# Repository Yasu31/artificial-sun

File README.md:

# Artificial Sun
[English README](/README-en.md)

自然な明かりで朝起きれる小型デバイス

ここではファームウェアのArduinoスケッチと基板デザイン(KiCad)を公開しています
- プロジェクト: https://yasunori.jp/pocket-sunrise
- 外装部品: https://grabcad.com/library/pocket-sunrise-1
- 動画: https://youtu.be/eCHGJ3ehzJc

## 電子部品
必要な電子パーツはこちらのスプレッドシートにまとめてあります。すべて秋月電子で買えます。
 →[Artificial Sun 電子部品](https://docs.google.com/spreadsheets/d/1AGpVGOaxi01ax8kF4fcREE8NY4uzkjkZFQBg4IJ91os/edit?usp=sharing)

## 基板
私はPCBGOGOに発注しましたがどこでも大丈夫だと思います。5枚発注して（初回割ということもありましたが）送料込みでたった1200円でした。

## 基板実装
以下の写真を参考に実装してください。注意点としては
- LEDの定格内で扱っていて、抵抗での発熱も許容範囲のはずですが、それでも想定外のケースなどで異常発熱する場合もあり得るので、使用時は常にそばにいる状態にしてください。自己責任で使ってください。
- 7セグ用の300Ω抵抗は一部のみ使い、それ以外は短絡してください（7セグの向きを後から変えられるようにこの実装になっています）。
- LEDの定格電流的には25Ωの電流制限抵抗は全然許容範囲内なのですが、セメント抵抗の方の発熱が大きかったので、50Ω抵抗を並列で接続して放熱板も取り付けることで発熱を抑えています。画像のように組付ければ、外装パーツ内に収まるはずです（もちろんちゃんとしたLEDドライバを使えば発熱を抑えられるのですが、初めての基板設計ということもあり簡単な回路を優先しました）
- Arduino nanoが基板に挿さったままだとスケッチが書き込めない場合があります。うまく書き込めない場合は、一旦抜いてから書き込んでください。
- LEDは10センチほどのワイヤで基板に接続してください。曲げやすいワイヤの方が外装パーツに挿入しやすいです。
- M3、長さ12mmのナットとボルト4本で組み立てられます。ゴム足パーツを底に貼ると滑り止めになります。

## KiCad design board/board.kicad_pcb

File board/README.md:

high-power LED circuit from https://nobulabo.com/power-led-blink/

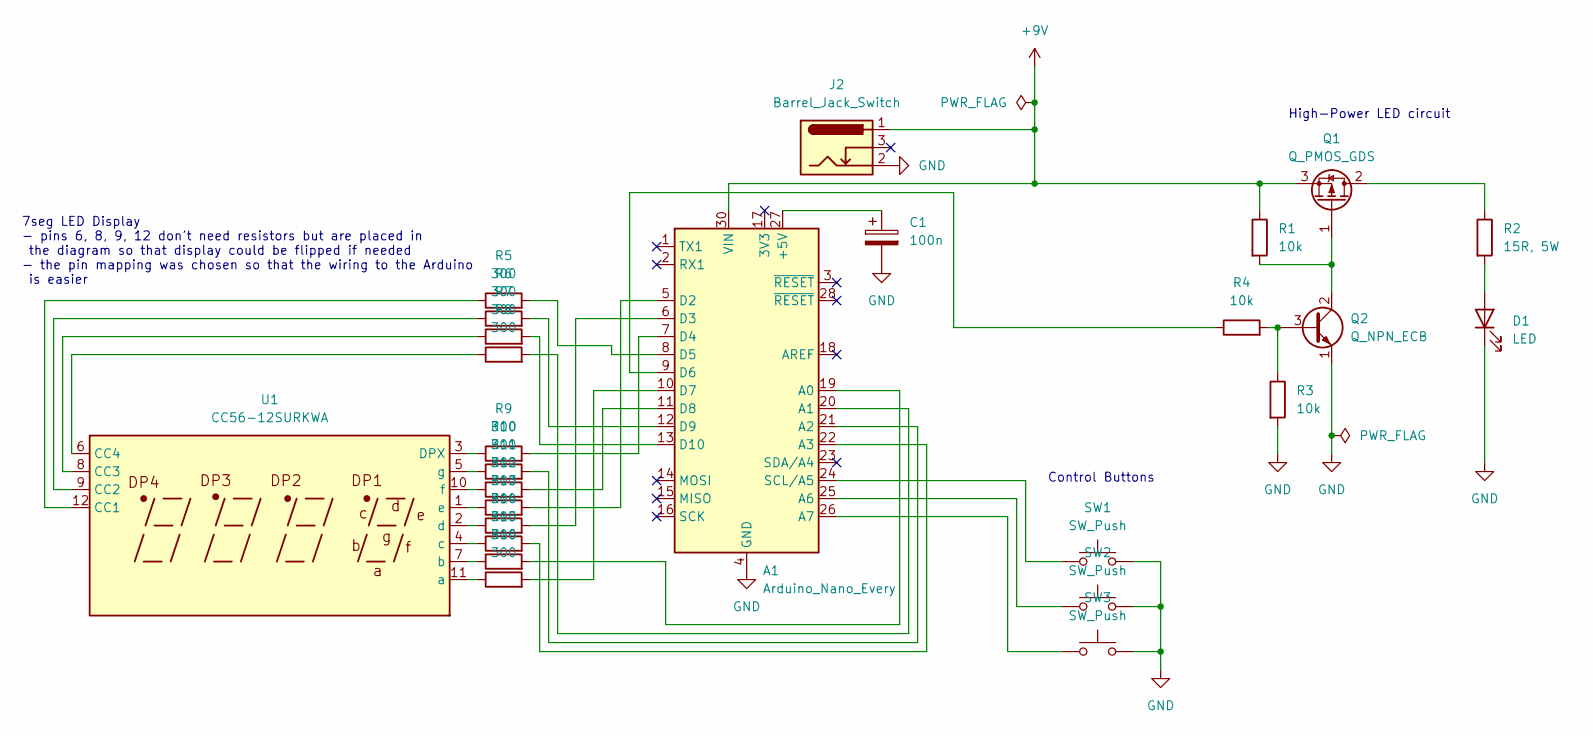
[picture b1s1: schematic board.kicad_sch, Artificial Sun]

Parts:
A1: Arduino_Nano_Every; Arduino_Nano
C1: 100n; C_Disc_D7.0mm_W2.5mm_P5.00mm
D1: LED; PinHeader_1x02_P2.54mm_Vertical
J2: Barrel_Jack_Switch; BarrelJack_Horizontal
Q1: Q_PMOS_GDS; TO-220-3_Horizontal_TabDown
Q2: Q_NPN_ECB; TO-92
R1, R3, R4: 10k; R_Axial_DIN0207_L6.3mm_D2.5mm_P10.16mm_Horizontal
R2: 15R, 5W; R_Axial_Power_L20.0mm_W6.4mm_P30.48mm
R5, R6, R7, R8, R9, R10, R11, R12, R13, R14, R15, R16: 300; R_Axial_DIN0207_L6.3mm_D2.5mm_P10.16mm_Horizontal
SW1, SW2, SW3: SW_Push; SW_PUSH_6mm_H7.3mm
U1: CC56-12SURKWA; CA56-12SURKWA

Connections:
+9V: A1.30 (VIN), J2.1, Q1.3 (S), R1.1
GND: A1.4 (GND), A1.29 (GND), C1.2, D1.1 (K), J2.2, Q2.1 (E), R3.2, SW1.2, SW2.2, SW3.2
unnamed: A1.27 (+5V), C1.1
unnamed: A1.19 (A0), R15.2
unnamed: A1.20 (A1), R8.2
unnamed: A1.21 (A2), R10.2
unnamed: A1.22 (A3), R14.2
unnamed: A1.25 (A6), SW2.1
unnamed: A1.26 (A7), SW3.1
unnamed: A1.5 (D2), R12.2
unnamed: A1.6 (D3), R13.2
unnamed: A1.7 (D4), R9.2
unnamed: A1.8 (D5), R5.2
unnamed: A1.9 (D6), R4.1
unnamed: A1.10 (D7), R16.2
unnamed: A1.11 (D8), R11.2
unnamed: A1.12 (D9), R6.2
unnamed: A1.13 (D10), R7.2
unnamed: A1.24 (SCL/A5), SW1.1
unnamed: D1.2 (A), R2.2
unnamed: Q1.2 (D), R2.1
unnamed: Q1.1 (G), Q2.2 (C), R1.2
unnamed: Q2.3 (B), R3.1, R4.2
unnamed: R5.1, U1.12 (CC1)
unnamed: R6.1, U1.9 (CC2)
unnamed: R7.1, U1.8 (CC3)
unnamed: R8.1, U1.6 (CC4)
unnamed: R9.1, U1.3 (DPX)
unnamed: R16.1, U1.11 (a)
unnamed: R15.1, U1.7 (b)
unnamed: R14.1, U1.4 (c)
unnamed: R13.1, U1.2 (d)
unnamed: R12.1, U1.1 (e)
unnamed: R11.1, U1.10 (f)
unnamed: R10.1, U1.5 (g)

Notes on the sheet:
7seg LED Display - pins 6, 8, 9, 12 don't need resistors but are placed in the diagram so that display could be flipped if needed - the pin mapping was chosen so that the wiring to the Arduino is easier
High-Power LED circuit
Control Buttons

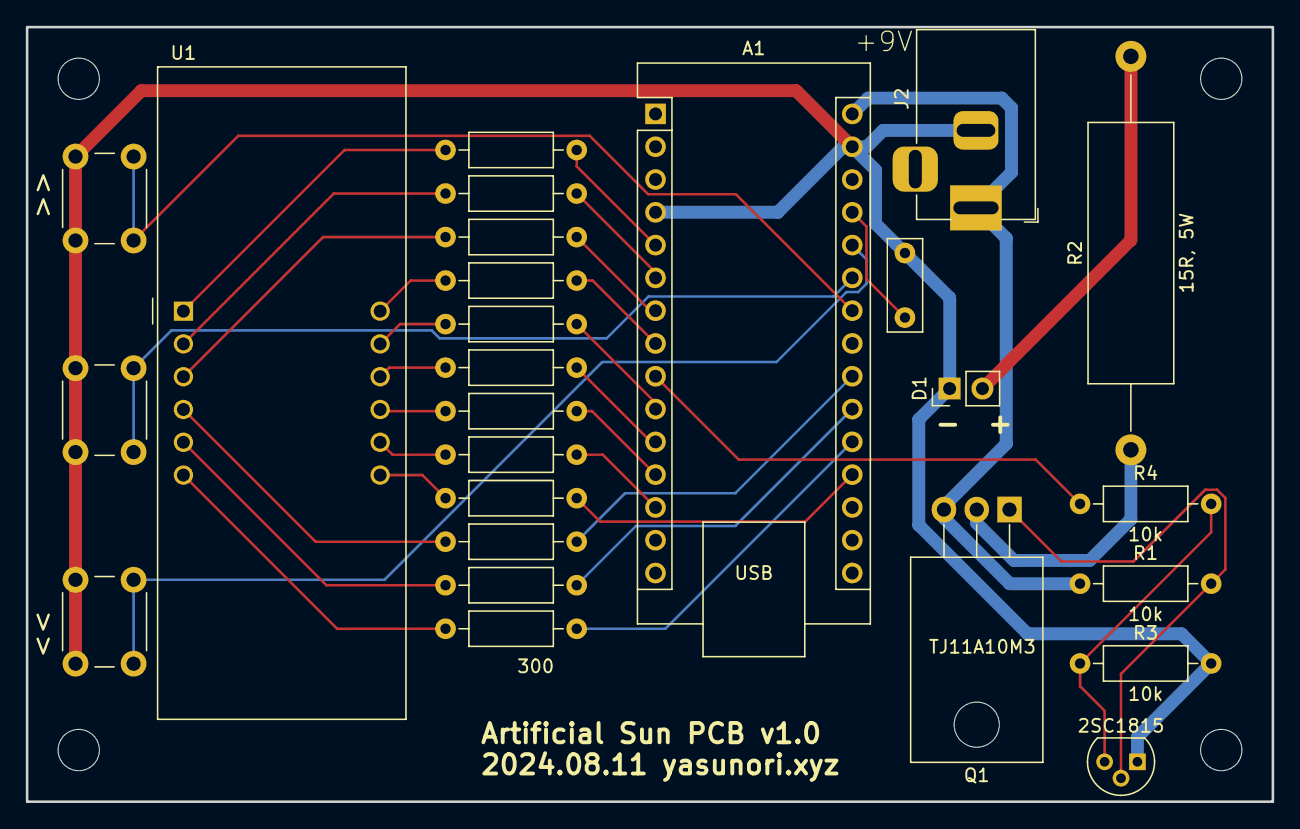
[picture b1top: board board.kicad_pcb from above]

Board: 2 copper layers, 96.5 x 60.0 mm, 26 parts (0 on the bottom side), 35 nets.

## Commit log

2020-12-07 sunset begins with warmer color, slightly longer sunrise sequence
2020-12-07 add to readme
2023-01-05 update for new IRremote library
2023-01-05 fix: convert mins to millis
2023-04-29 automatic turn off
2024-08-08 initial commit for kicad
2024-08-10 implement part of the wiring
2024-08-10 complete the design
2024-08-11 edit silkscreen
2024-08-11 more compact board
2024-08-11 set thick lines for LEDs, probably ready for manufacture
2024-08-13 move some symbols on silk screen layer
2024-08-24 v1 board
2024-08-24 rename
2024-08-24 add render
2024-08-24 add initial sketch
2024-08-25 add step file
2024-08-26 add sample code for sevseg and LED
2024-08-29 example to increment counter when button is pressed
2024-08-29 use exponential scale to natually scale brightness
2024-09-28 initial full version done!
2024-10-07 - accelerate "scroll" speed when button is kept pressed, so user can adjust large values easier - for safety: turn off LED after some time even if the user doesn't turn it off after the timer goes to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
2024-10-07 - don't blink the display while adjusting the time, even though it is paused - when the display is off, pushing a button should only wake up the display and do nothing else - the scroll "acceleration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
2024-10-07 refactor to simplify
2024-10-07 Refactor brightness calculation to include sinusoidal pulsing effect
2024-10-11 fix it so sinusoidal pulsing continues after timer is off
2024-10-11 also add "sunset" sequence
2024-10-13 fix: unintended block executed near end of timer, better documentation and ordering of code
2024-10-13 Refactor brightness calculation to ensure PWM value ranges from 0 to 255
2024-10-14 fix the LED completely turning off
2024-11-23 add more info
2024-11-23 Create LICENSE
